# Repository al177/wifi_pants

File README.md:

# wifi_pants
The dawn of the IoP era

Released under the [Creative Commons Share Alike (CC-BY-SA) License](https://creativecommons.org/licenses/by-sa/4.0/).  Share it, change it, make money on it, teach it to the children as a cautionary tale.  Just make your changes public and give credit to all contributors to this project.

Attributions:

Andrew Litt (dev)

Jerry Dunmire (for the esp8266 Kicad library https://github.com/jdunmire/kicad-ESP8266)

Mike Cousins (for the nice mcous discrete footprints https://github.com/mcous/kicad-lib)

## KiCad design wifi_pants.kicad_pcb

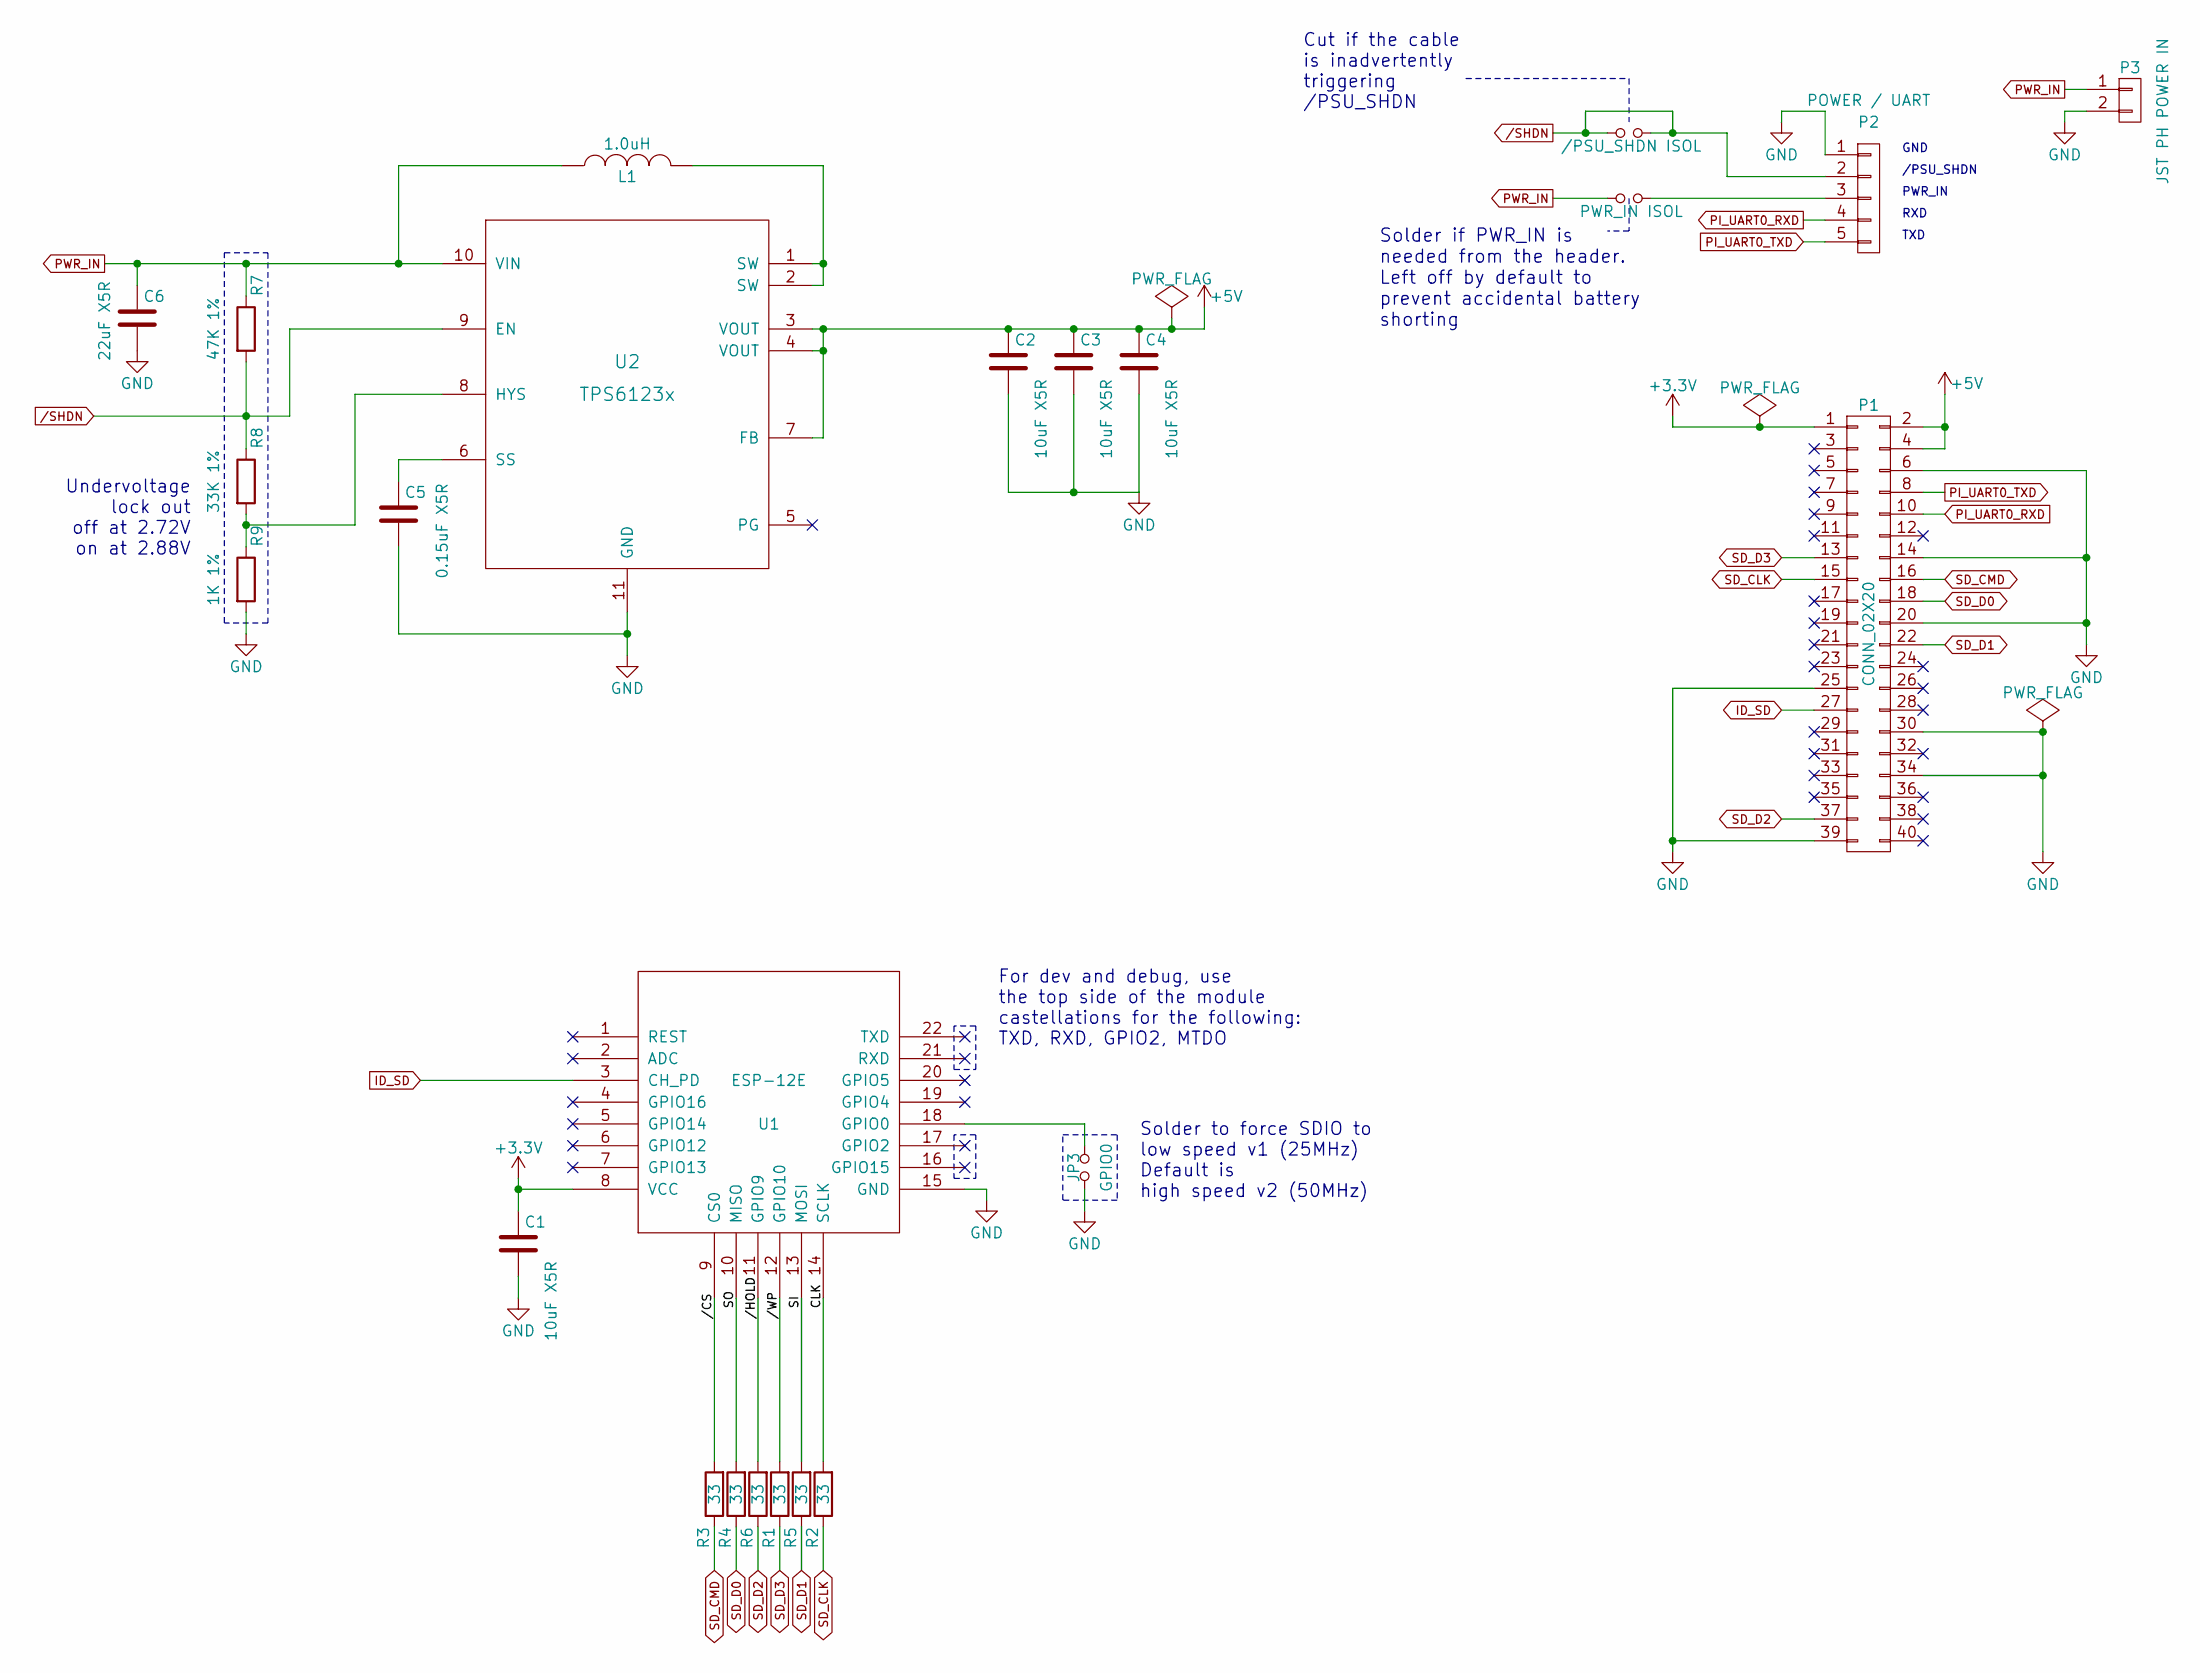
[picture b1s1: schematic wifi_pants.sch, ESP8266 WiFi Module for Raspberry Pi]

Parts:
C1, C2, C3, C4: 10uF X5R; 0805(2012m)-CHIP-CAP; MFG Part Num LMK212BJ106KG-T; Digikey PN 587-1300-1-ND
C5: 0.15uF X5R; 0603(1608m)-CHIP-CAP; MFG Part Num GRM188R61A154KA01D; Digikey PN 490-11495-1-ND
C6: 22uF X5R; 0805(2012m)-CHIP-CAP; MFG Part Num LMK212BJ226MG-T; Digikey PN 587-1958-1-ND
JP1: /PSU_SHDN ISOL; GS2
JP2: PWR_IN ISOL; GS2
JP3: GPIO0; GS2; MFG Part Num NA
L1: 1.0uH; SRU1028-1R; MFG Part Num SRU1028-1R0Y; Digikey PN SRU1028-1R0YCT-ND
P1: CONN_02X20; Socket_Strip_Straight_2x20_pi; MFG Part Num 2223; Digikey PN 1528-1385-ND
P2: POWER / UART; Pin_Header_Angled_1x05_mirror; MFR Part Num PRPC005SBAN-M71RC; Digikey PN S1111EC-05-ND
P3: JST PH POWER IN; Connectors_JST_S2B-PH-K; MFR Part Num S2B-PH-K-S(LF)(SN); Digikey PN 455-1719-ND
R1, R2, R3, R4, R5, R6: 33; 0603(1608m)-CHIP-RESISTOR; MFG Part Num ERJ-3EKF33R0V; Digikey PN P33.0HCT-ND
R7: 47K 1%; 0603(1608m)-CHIP-RESISTOR; MFG Part Num ERJ-3EKF4702V; Digikey PN P47.0KHCT-ND
R8: 33K 1%; 0603(1608m)-CHIP-RESISTOR; MFG Part Num ERJ-3EKF3302V; Digikey PN P33.0KHCT-ND
R9: 1K 1%; 0603(1608m)-CHIP-RESISTOR; MFG Part Num ERJ-3EKF1001V; Digikey PN P1.00KHCT-ND
U1: ESP-12E; ESP-12E-narrow
U2: TPS6123x; VSON-10; MFR Part Num TPS61232DRC; Digikey PN 296-37990-1-ND

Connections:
+3V3: C1.1, P1.1, U1.8 (VCC)
+5V: C2.1, C3.1, C4.1, P1.2, P1.4, U2.3 (VOUT), U2.4 (VOUT), U2.7 (FB)
//CS: R3.2, U1.9 (CS0)
//HOLD: R6.2, U1.11 (GPIO9)
//WP: R1.2, U1.12 (GPIO10)
/CLK: R2.2, U1.14 (SCLK)
/SHDN: JP1.1, JP1.2, P2.2, R7.2, R8.1, U2.9 (EN)
/SI: R5.2, U1.13 (MOSI)
/SO: R4.2, U1.10 (MISO)
GND: C1.2, C2.2, C3.2, C4.2, C5.2, C6.2, JP3.2, P1.6, P1.14, P1.20, P1.25, P1.30, P1.34, P1.39, P2.1, P3.2, R9.2, U1.15 (GND), U2.11 (GND)
ID_SD: P1.27, U1.3 (CH_PD)
unnamed: C5.1, U2.6 (SS)
unnamed: JP2.2, P2.3
unnamed: JP3.1, U1.18 (GPIO0)
unnamed: L1.2, U2.1 (SW), U2.2 (SW)
unnamed: R8.2, R9.1, U2.8 (HYS)
PI_UART0_RXD: P1.10, P2.4
PI_UART0_TXD: P1.8, P2.5
PWR_IN: C6.1, JP2.1, L1.1, P3.1, R7.1, U2.10 (VIN)
SD_CLK: P1.15, R2.1
SD_CMD: P1.16, R3.1
SD_D0: P1.18, R4.1
SD_D1: P1.22, R5.1
SD_D2: P1.37, R6.1
SD_D3: P1.13, R1.1

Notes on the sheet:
GND
TXD
RXD
For dev and debug, use the top side of the module castellations for the following: TXD, RXD, GPIO2, MTDO
Solder to force SDIO to low speed v1 (25MHz) Default is high speed v2 (50MHz)
/PSU_SHDN
PWR_IN
Cut if the cable is inadvertently triggering /PSU_SHDN
Undervoltage lock out off at 2.72V on at 2.88V
Solder if PWR_IN is needed from the header. Left off by default to prevent accidental battery shorting

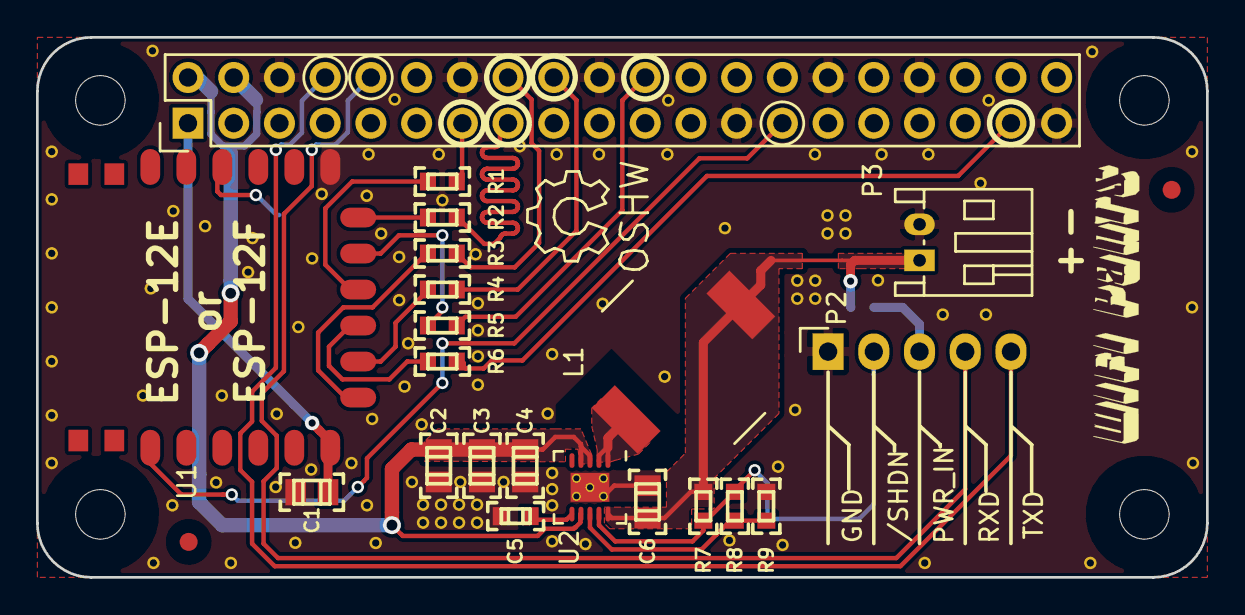
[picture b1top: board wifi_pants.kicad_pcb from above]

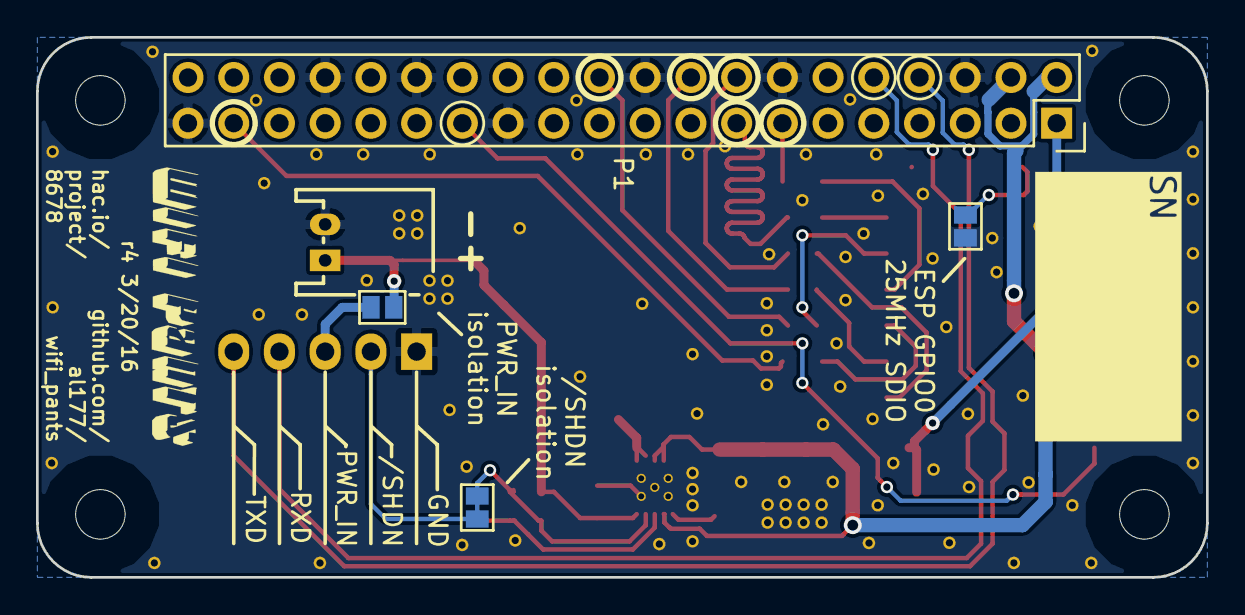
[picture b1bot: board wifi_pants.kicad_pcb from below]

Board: 2 copper layers, 65.0 x 30.0 mm, 28 parts (4 on the bottom side), 25 nets.

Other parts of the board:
W1, W1#2, W1#3, W1#4: MOUNT; NPTH_Hole_2_75mm

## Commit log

2016-01-15 Add UART header, clean up routing
2016-01-16 Add audio and expanded header
2016-01-16 Stitch edge, start cleaning up
2016-01-16 Add audio, change header to include audio and +5V in, cleanup silk
2016-01-17 Add logo
2016-01-17 Order r1, check in r1 gerbers
2016-01-18 Add schematic PDF
2016-01-18 Add 3d views with back mount long pin connector
2016-01-28 r2 schematic and layout
    Changes:
    -move module antenna offboard to clear the Pi board and components
    -SDIO is now routed over a solid ground plane
    -remove test points for UART TX/RX on the module. these can be
    picked off the module topside
    -Default to ID_SD as the CHIP_EN default drive.
2016-02-07 start adding boost converter
2016-02-10 Remove audio, place connectors, new 4-bit SDIO routing
2016-02-12 Layout switcher, clean up
2016-02-13 Changed to a different switcher
2016-02-13 Clean up PSU layout and silk
2016-02-14 v3 complete layout
2016-02-14 Fab files for v3
2016-02-18 Fix some part#s in the schematic, clean up the back side silk for the JST connector
2016-03-09 Add UVLO for LiPo, rearrange boost layout, make PWR_IN on header disconnected by default
2016-03-20 logo and serial number added
2016-03-20 r4 fab files
2016-03-27 Update PDF schematic to r4

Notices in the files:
wifi_pants.kicad_pcb:
Licensed under Creative Commons Attribution Share-Alike
